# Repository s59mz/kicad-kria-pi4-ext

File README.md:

# kicad-kria-pi4-ext
Extension adapter module for the Kria KR260, providing a Pi-4 port to Z-turn port intended for using multiple Alinx modules and PMOD interfaces.

Schematic:
[kicad-kria-pi4-ext.pdf](kicad-kria-pi4-ext.pdf)

BOM:
[kicad-kria-pi4-ext.csv](kicad-kria-pi4-ext.csv)

Gerbers:
[gerbers.zip](https://github.com/s59mz/kicad-kria-pi4-ext/raw/main/gerbers.zip)

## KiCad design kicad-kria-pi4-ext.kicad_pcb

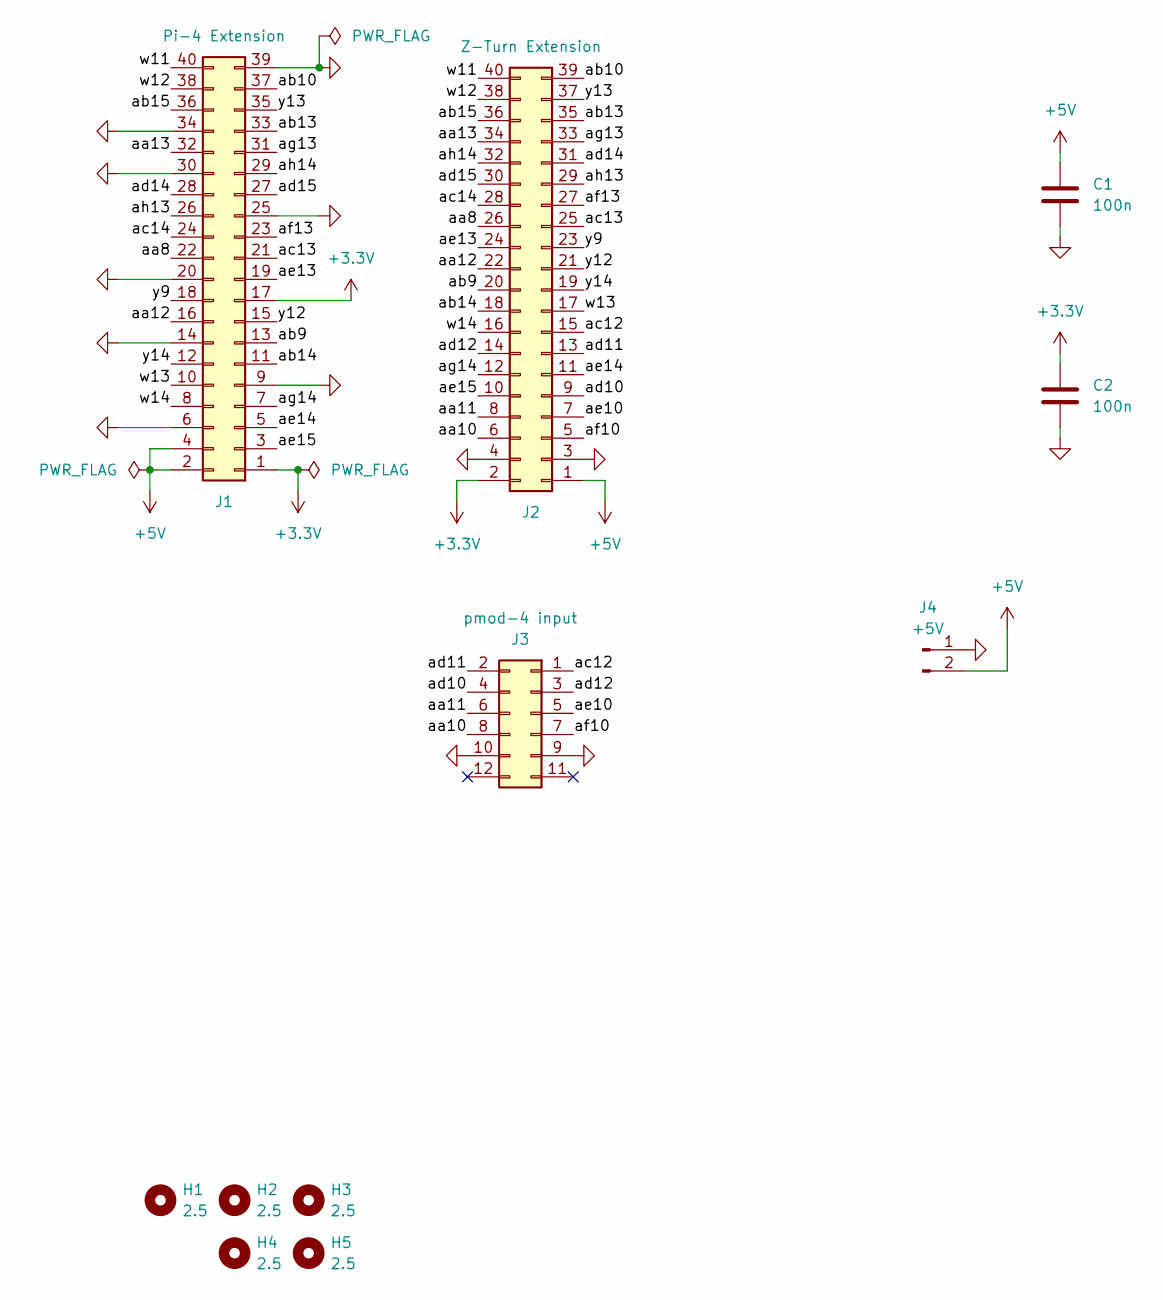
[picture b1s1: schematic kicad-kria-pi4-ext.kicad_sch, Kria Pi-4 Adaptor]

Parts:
C1, C2: 100n; C_0603_1608Metric_Pad1.08x0.95mm_HandSolder
H1, H2, H3, H4, H5: 2.5; MountingHole_2.5mm
J1: Pi-4 Extension; PinSocket_2x20_P2.54mm_Vertical
J2: Z-Turn Extension; PinHeader_2x20_P2.54mm_Vertical
J3: pmod-4 input; IDC-Header_2x06_P2.54mm_Vertical
J4: +5V; PinHeader_1x02_P2.54mm_Vertical

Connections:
+3.3V: C2.1, J1.1, J1.17, J2.2
+5V: C1.1, J1.2, J1.4, J2.1, J4.2
/aa8: J1.22, J2.26
/aa10: J2.6, J3.8
/aa11: J2.8, J3.6
/aa12: J1.16, J2.22
/aa13: J1.32, J2.34
/ab9: J1.13, J2.20
/ab10: J1.37, J2.39
/ab13: J1.33, J2.35
/ab14: J1.11, J2.18
/ab15: J1.36, J2.36
/ac12: J2.15, J3.1
/ac13: J1.21, J2.25
/ac14: J1.24, J2.28
/ad10: J2.9, J3.4
/ad11: J2.13, J3.2
/ad12: J2.14, J3.3
/ad14: J1.28, J2.31
/ad15: J1.27, J2.30
/ae10: J2.7, J3.5
/ae13: J1.19, J2.24
/ae14: J1.5, J2.11
/ae15: J1.3, J2.10
/af10: J2.5, J3.7
/af13: J1.23, J2.27
/ag13: J1.31, J2.33
/ag14: J1.7, J2.12
/ah13: J1.26, J2.29
/ah14: J1.29, J2.32
/w11: J1.40, J2.40
/w12: J1.38, J2.38
/w13: J1.10, J2.17
/w14: J1.8, J2.16
/y9: J1.18, J2.23
/y12: J1.15, J2.21
/y13: J1.35, J2.37
/y14: J1.12, J2.19
GND: C1.2, C2.2, J1.6, J1.9, J1.14, J1.20, J1.25, J1.30, J1.34, J1.39, J2.3, J2.4, J3.9, J3.10, J4.1

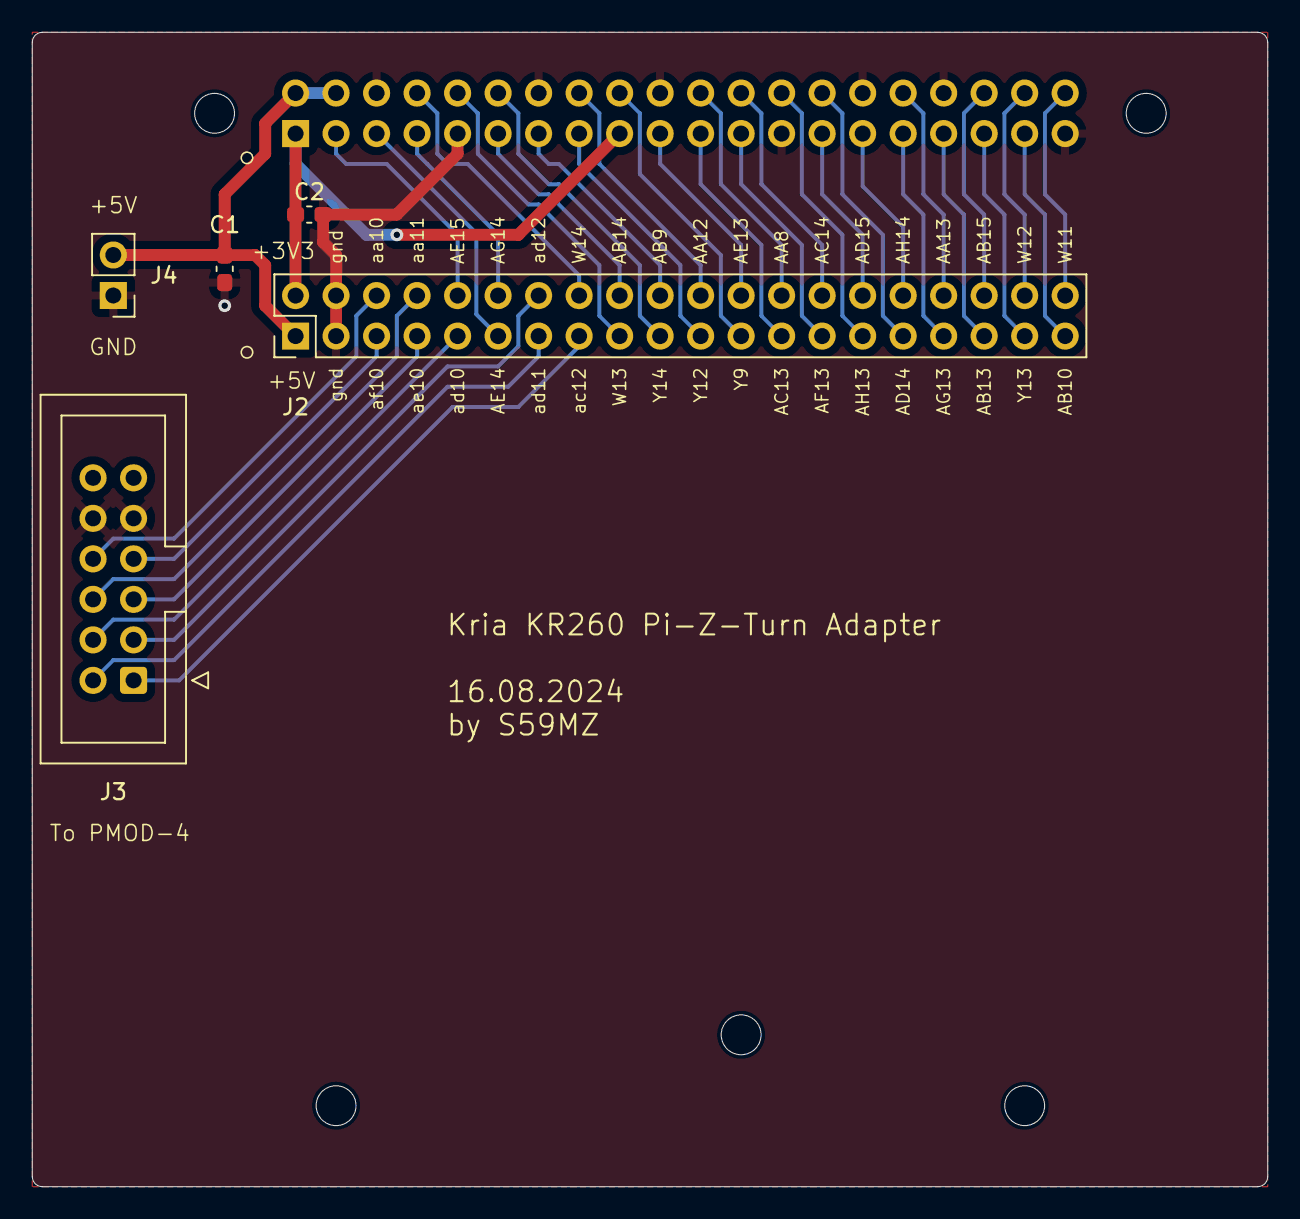
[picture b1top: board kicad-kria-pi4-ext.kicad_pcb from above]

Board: 2 copper layers, 77.5 x 72.4 mm, 11 parts (1 on the bottom side), 39 nets.
